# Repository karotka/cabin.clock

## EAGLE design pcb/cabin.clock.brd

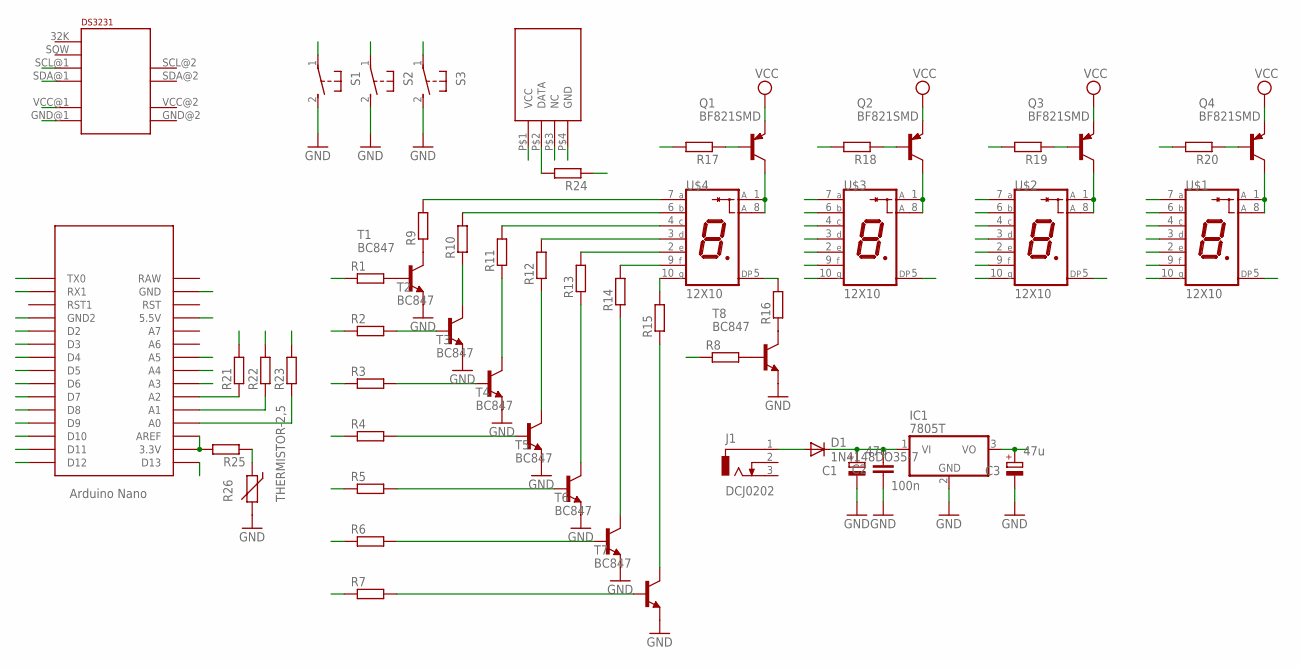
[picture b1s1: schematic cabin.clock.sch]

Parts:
C1, C3: 47u; PANASONIC_D
C2: 100n; C1206
D1: 1N4148DO35-7; DO35-7
IC1: 7805T; TO220H
J1: DCJ0202
Q1, Q2, Q3, Q4: BF821SMD; SOT23-BEC
R1, R2, R3, R4, R5, R6, R7, R8, R9, R10, R11, R12, R13, R14, R15, R16, R17, R18, R19, R20, R21, R22, R23, R24, R25: R-EU_0207/10; 0207/10
R26: THERMISTOR-2,5; RS-2,5
S1, S2, S3: 31-XX; B3F-31XX
T1, T2, T3, T4, T5, T6, T7, T8: BC847; SOT23
U$1, U$2, U$3, U$4: 12X10
U$5: NANO
U$6: DS3231BOARD; BOARD
U$7: DTH21

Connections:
A: R9.2, U$1.7 (A), U$2.7 (A), U$3.7 (A), U$4.7 (A)
A0: R23.1, S1.1, U$5.A0
A1: R22.1, S2.1, U$5.A1
A2: R21.1, S3.1, U$5.A2
A3: R25.1, R26.1, U$5.A3
B: R10.2, U$1.6 (B), U$2.6 (B), U$3.6 (B), U$4.6 (B)
C: R11.2, U$1.4 (C), U$2.4 (C), U$3.4 (C), U$4.4 (C)
D: R12.2, U$1.3 (D), U$2.3 (D), U$3.3 (D), U$4.3 (D)
D2: R3.1, U$5.D2
D3: R4.1, U$5.D3
D4: R5.1, U$5.D4
D5: R6.1, U$5.D5
D6: R7.1, U$5.D6
D7: R8.1, U$5.D7
D8: R17.2, U$5.D8
D9: R18.2, U$5.D9
D10: R19.2, U$5.D10
D11: R20.2, U$5.D11
D12: U$5.D12
D13: R24.2, U$5.D13, U$7.P$2 (DATA)
DP: R16.2, U$1.5 (DP), U$2.5 (DP), U$3.5 (DP), U$4.5 (DP)
E: R13.2, U$1.2 (E), U$2.2 (E), U$3.2 (E), U$4.2 (E)
F: R14.2, U$1.9 (F), U$2.9 (F), U$3.9 (F), U$4.9 (F)
G: R15.2, U$1.10 (G), U$2.10 (G), U$3.10 (G), U$4.10 (G)
GND: C1.-, C2.2, C3.-, IC1.2 (GND), R26.2, S1.2 (S), S2.2 (S), S3.2 (S), T1.2 (E), T2.2 (E), T3.2 (E), T4.2 (E), T5.2 (E), T6.2 (E), T7.2 (E), T8.2 (E), U$5.GND, U$5.GND1 (GND2), U$6.GND@1 (GND), U$6.GND@2 (GND), U$7.P$4 (GND)
unnamed: R1.2, T1.1 (B)
unnamed: R8.2, T8.1 (B)
unnamed: Q4.C, U$1.1 (A), U$1.8 (A)
unnamed: R9.1, T1.3 (C)
unnamed: Q3.C, U$2.1 (A), U$2.8 (A)
unnamed: R16.1, T8.3 (C)
unnamed: Q2.C, U$3.1 (A), U$3.8 (A)
unnamed: Q1.C, U$4.1 (A), U$4.8 (A)
unnamed: Q1.B, R17.1
unnamed: Q2.B, R18.1
unnamed: Q3.B, R19.1
unnamed: Q4.B, R20.1
unnamed: D1.A, J1.1
unnamed: R25.2, U$5.3.3V, U$5.AREF
unnamed: R10.1, T2.3 (C)
unnamed: R11.1, T3.3 (C)
unnamed: R12.1, T4.3 (C)
unnamed: R13.1, T5.3 (C)
unnamed: R14.1, T6.3 (C)
unnamed: R15.1, T7.3 (C)
unnamed: R2.2, T2.1 (B)
unnamed: R3.2, T3.1 (B)
unnamed: R4.2, T4.1 (B)
unnamed: R5.2, T5.1 (B)
unnamed: R6.2, T6.1 (B)
unnamed: R7.2, T7.1 (B)
RX1: R1.1, U$5.RX1
SCL: U$5.A5, U$6.SCL@1 (SCL)
SDA: U$5.A4, U$6.SDA@1 (SDA)
TX0: R2.1, U$5.TX0
VCC: C3.+, IC1.3 (VO), R21.2, R22.2, R23.2, R24.1, U$5.5V (5.5V), U$6.VCC@1 (VCC), U$6.VCC@2 (VCC), U$7.P$1 (VCC)
VIN: C1.+, C2.1, D1.C, IC1.1 (VI), Q1.E, Q2.E, Q3.E, Q4.E

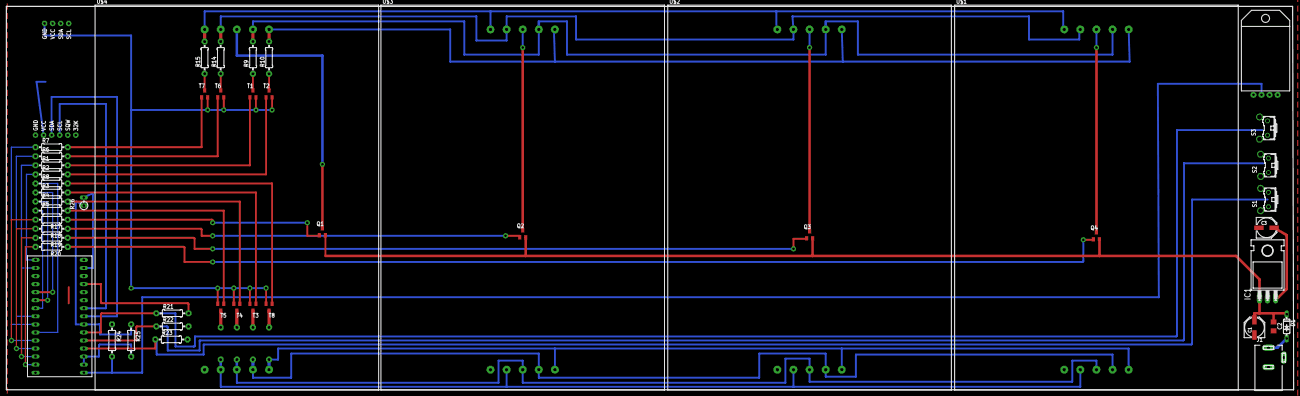
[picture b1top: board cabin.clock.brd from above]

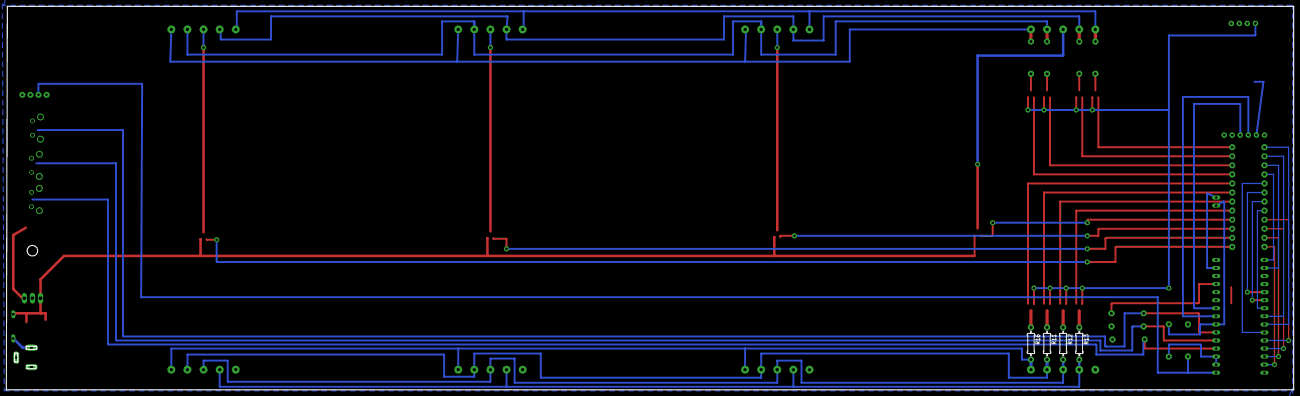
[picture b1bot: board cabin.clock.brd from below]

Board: 2 copper layers, 406.1 x 121.0 mm, 54 parts (4 on the bottom side), 56 nets.
